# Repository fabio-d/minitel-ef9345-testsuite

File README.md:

# EF9345/TS9347 test suite

This repository contains a test suite for emulators of the
[EF9345](https://en.wikipedia.org/wiki/Thomson_EF9345) and TS9347 video chips,
such as the one included in the [MAME project](https://www.mamedev.org/).

These video chips provided the graphic capabilities of many French
[Minitels](https://en.wikipedia.org/wiki/Minitel) in the 80s and 90s.

The tests in this repository can be run both against MAME (see
[emu_mame](emu_mame) subfolder) and against real chips, through a custom USB
adapter board (see [hw_devboard](hw_devboard) subfolder).

While it is possible (and, currently, expected) that some tests may not pass on
MAME, all the tests have been verified on real chips.

## License

Same as MAME, i.e. [GNU General Public License version 2](LICENSE) or later.

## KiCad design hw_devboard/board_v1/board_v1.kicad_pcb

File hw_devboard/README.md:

# Hardware board: USB EF9345/TS9347 Video Adapter

This folder contains the schematics, firmware and host software for running the
test suite against real EF9345 and TS9347 chips using a custom board.

## Board description

The custom boards host the video chip (either EF9345P or TS9347CP/2R00), a 32
KiB RAM module for it to store the text buffers and a 74LS373N latch to
demultiplex RAM addresses. In addition, for the TS9347CP only, an LM393 and some
passives extract the video composite sync signal from the TS9347CP's analog Y
output.

The solder jumper pads (JP1 to JP9) on the back side of the board adapt some
internal connections to the connected video chip (the EF9345P and TS9347CP/2R00
are not pin compatible).

Jumpers JP11-JP14 make it possible to limit the available RAM size.

Bill of materials with links:

* U1: The video chip
  ([EF9345P](https://www.aliexpress.com/item/32905550985.html) or
  [TS9347CP/2R00](https://www.ebay.com/itm/281664411315)) and
  [its socket (40 pin variant)](https://www.aliexpress.com/item/1005006256010892.html).
* U2: [AS6C62256-55PCN](https://www.mouser.com/ProductDetail/913-AS6C62256-55PCN)
  SRAM and [its socket](https://www.mouser.com/ProductDetail/737-ICS-628-T).
* U3: [SN74LS373N](https://www.mouser.com/ProductDetail/595-SN74LS373N) and
  [its socket](https://www.mouser.com/ProductDetail/737-ICS-320-T).
* U4 (for the TS9347 only): LM393 and its socket (e.g. from
  [this kit](https://www.aliexpress.com/item/1005007032661721.html)).
* RV1 (for the TS9347 only): 200 kOhm RM065 potentiometer (e.g. from
  [this kit](https://www.aliexpress.com/item/1005006182414764.html)).
* R1 (for the TS9347 only): 220 kOhm resistor.
* R2 (for the TS9347 only): 4.7 kOhm resistor.
* C1 and C2 (for the TS9347 only): 10 uF electrolitic capacitors.
* 2.54 mm male and female pin headers (e.g. from
  [this kit](https://www.aliexpress.com/item/1005006034877497.html)).
* 3 (EF9345) or 4 (TS9347) 2.54 mm jumpers (e.g. from
  [this kit](https://www.aliexpress.com/item/4000583368141.html)).

In addition, the board itself needs to be mounted on the
[EZ-USB FX2LP development board](https://www.aliexpress.com/item/1005005100640836.html),
which provides the high-speed USB interface to both read/write the video chip's
registers and, most importantily, streaming the real-time video signal back to
the host computer at 12 MiB/s.

### EZ-USB FX2LP board pinout

| FX2 pin     | EF9345P pin | TS9347CP/2R00 pin | Description                  |
|-------------|-------------|-------------------|------------------------------|
| **Outputs:**                                                              ||||
| CTL0 (J2.16)| CLK (12)    | CLK (12)          | Video Chip Clock             |
| PA3 (J2.10) | AS (14)     | AS (14)           | Address Strobe (aka ALE)     |
| PA4 (J2.9)  | DS (15)     | DS (15)           | Data Strobe (aka ~RD)        |
| PA5 (J2.8)  | R/~W (16)   | R/~W (16)         | Read/Write (aka ~WR)         |
| PA6 (J2.7)  | ~CS (26)    | ~CS (20)          | Chip Select                  |
| **Inputs:**                                                               ||||
| PB0 (J1.15) | I (10)      | G (10)            | Video Signal Value (digital) |
| PB1 (J1.16) | R (9)       | R (9)             | Video Signal Value (digital) |
| PB2 (J1.17) | G (8)       | B (8)             | Video Signal Value (digital) |
| PB3 (J1.18) | B (7)       | not connected     | Video Signal Value (digital) |
| PB6 (J2.18) |             |                   | CTL0 loopback (for debug)    |
| PB7 (J2.17) | HVS/HS (5)  | Y (7) via LM393   | Video Signal Composite Sync  |
| **Bidirectional:**                                                        ||||
| PD0 (J2.5)  | AD0 (17)    | AD0 (17)          | Multiplexed Address/Data Bus |
| PD1 (J2.4)  | AD1 (18)    | AD1 (18)          | Multiplexed Address/Data Bus |
| PD2 (J2.3)  | AD2 (19)    | AD2 (19)          | Multiplexed Address/Data Bus |
| PD3 (J2.2)  | AD3 (21)    | AD3 (21)          | Multiplexed Address/Data Bus |
| PD4 (J2.1)  | AD4 (22)    | AD4 (22)          | Multiplexed Address/Data Bus |
| PD5 (J1.1)  | AD5 (23)    | AD5 (23)          | Multiplexed Address/Data Bus |
| PD6 (J1.2)  | AD6 (24)    | AD6 (24)          | Multiplexed Address/Data Bus |
| PD7 (J1.3)  | AD7 (25)    | AD7 (25)          | Multiplexed Address/Data Bus |

Note: When EZ-USB's J3 jumper is inserted, PA0 and PA1 control the on-board LEDs
(respectively D1 and D2). Our firmware reports what kind of chip it detected
through these LEDs: EF9345 = D1 on, TS9347 = D2 on, detection failed = both on.

### Schematic

## Customization

Before using the board, some customizations are necessary.

### Selecting the video chip

JP1 to JP9 on the back side of the board need to be bridged with solder,
depending on the type of video chip to be tested:

* each JPx must be bridged to the left (i.e. by shorting pads 1 and 2) for the
  EF9345P, like in the picture above.
* each JPx must be bridged to the right (i.e. by shorting pads 2 and 3) for the
  TS9347CP/2R00, symmetrical to the picture above.

In addition, for the TS9347CP only, the RV1 potentiometer must be adjusted so
that its middle pin gives about 0.456 V (to tell the SYNC and BLACK levels
apart, see the "REFERENCE LEVEL" table in the TS9347 datasheet).

### Selecting the video RAM size

Provided neither long codes nor custom fonts are used, the EF9345 and TS9347 can
operate with as little as just 2 KiB of video RAM.

While the AS6C62256-55PCN RAM IC contains 32 KiB of RAM, it is possible to mask
some of its address lines through jumpers JP11-JP14 to make it appear smaller.
The following configurations are possible:

<table>
  <tr>
    <td align="center"><br />2 K</td>
    <td align="center"><br />4 K</td>
    <td align="center"><br />8 K</td>
    <td align="center"><br />16 K</td>
    <td align="center"><br />32 K</td>
  </tr>
</table>

Note 1: JP14 is ignored and can be left unpopulated in the case of the EF9345
chip, as EF9345 only supports up to 16 KiB.

Note 2: current and future tests will assume that all the jumpers are connected
to the right (i.e. maximum possible RAM size).

### Getting 5 V power from the EZ-USB FX2LP development board

All the chips on our board (including, notably, the video chip) need to be
powered at 5 V. The USB power supply provided from the host would be suitable
(the USB bus provides power at exactly 5 V) but, unfortunately, no pin of the
EZ-USB FX2LP development board exposes the USB's 5 V line.

Therefore, in order to connect USB's 5 V to our board, we need to apply a small
mod to the EZ-USB FX2LP board by soldering and connecting a wire as shown in the
following images:

Note: by soldering the wire in the way shown above, the power switch on the
front of the EZ-USB FX2LP board will be in control of our derived 5 V rail too.

### Supporting software

Prerequisites:

```shell
$ git submodule init && git submodule update  # to checkout firmware/fx2lib
$ sudo apt install build-essential cycfx2prog libusb-1.0-0-dev qt6-base-dev sdcc
```

Firmware for the FX2LP chip is provided in the `firmware` subdirectory and it
can be compiled and then loaded over USB into the board with:

```shell
$ cd hw_devboard/firmware
$ make
$ sudo cycfx2prog prg:build/firmware.ihx run
```

The above `cycfx2prog` command will load the firmware into the FX2LP's RAM and
execute it from there. It will not persist after power cycling.

The `host_connector_gui` program can then be started on the host:

```shell
$ cd hw_devboard/host_connector_gui
$ qmake6
$ make
$ sudo ./host_connector_gui
```

## Running the tests

After loading the firmware and opening the `host_connector_gui` program, select
*Device* &rarr; *Connect...* to locate the USB board, then *Device* &rarr;
*Enable TCP Server...* and confirm the default listen address `127.0.0.1:1234`.

Finally, run a test (e.g. `test_resolutions.py`) with:

```shell
$ cd ../tests
$ python3 test_resolutions.py --video-chip 127.0.0.1:1234
```

## Gallery

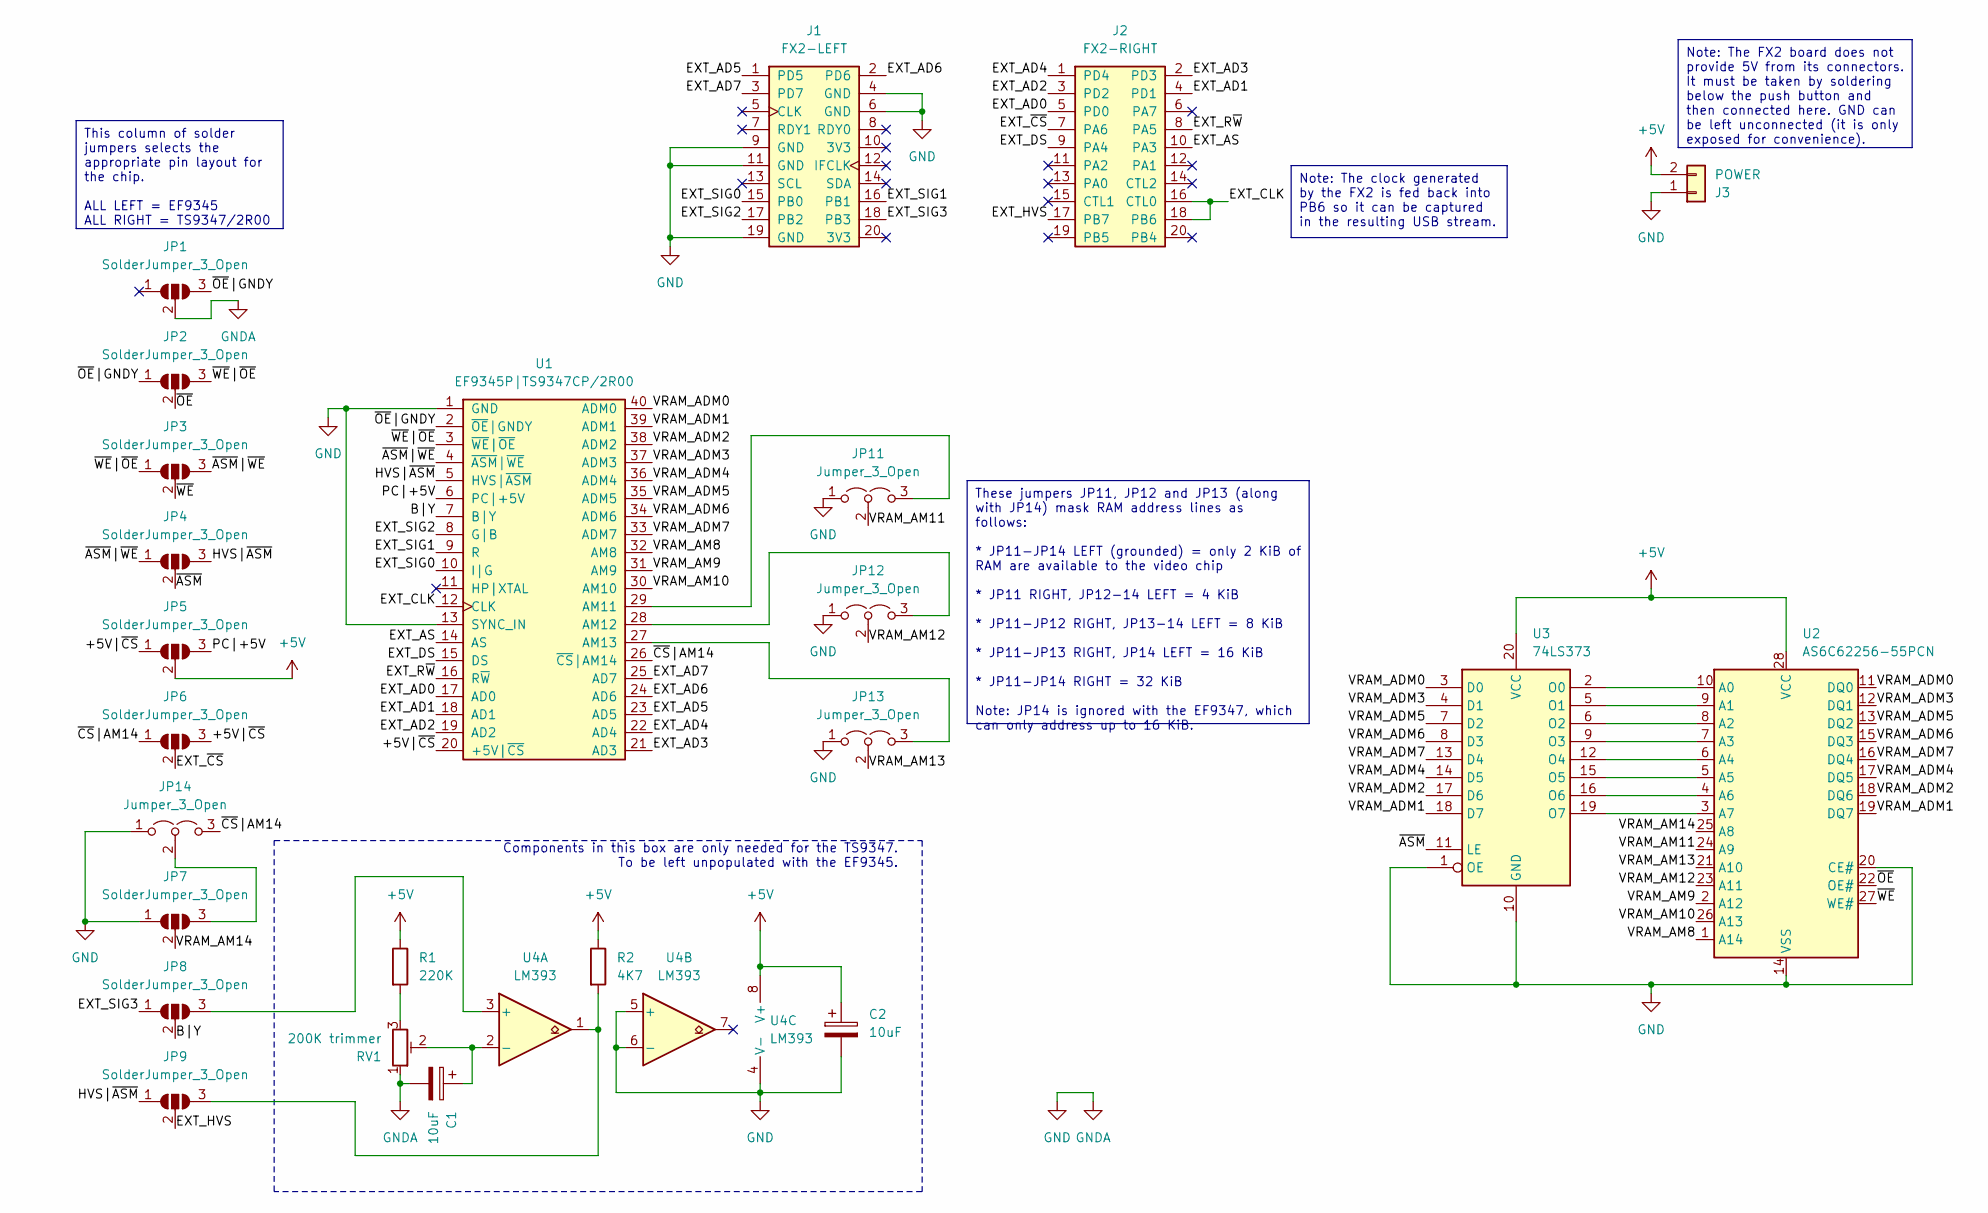
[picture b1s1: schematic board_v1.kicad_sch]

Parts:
C1, C2: 10uF; CP_Radial_D5.0mm_P2.50mm
J1: FX2-LEFT; PinHeader_2x10_P2.54mm_Vertical
J2: FX2-RIGHT; PinHeader_2x10_P2.54mm_Vertical
J3: POWER; PinHeader_1x02_P2.54mm_Vertical
JP1, JP2, JP3, JP4, JP5, JP6, JP7, JP8, JP9: SolderJumper_3_Open; SelectorJumper
JP11, JP12, JP13, JP14: Jumper_3_Open; PinHeader_1x03_P2.54mm_Vertical
R1: 220K; R_Axial_DIN0309_L9.0mm_D3.2mm_P12.70mm_Horizontal
R2: 4K7; R_Axial_DIN0309_L9.0mm_D3.2mm_P12.70mm_Horizontal
RV1: 200K trimmer; Potentiometer_Runtron_RM-065_Vertical
U1: EF9345P|TS9347CP/2R00; DIP-40_W15.24mm_Socket
U2: AS6C62256-55PCN; DIP-28_W15.24mm
U3: 74LS373; DIP-20_W7.62mm_Socket
U4: LM393; DIP-8_W7.62mm_Socket

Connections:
+5V: C2.1, J3.2, JP5.2 (C), R1.1, R2.1, U2.28 (VCC), U3.20 (VCC), U4.8 (V+)
/+5V|~CS: JP5.1 (A), JP6.3 (B), U1.20 (+5V|~CS)
/B|Y: JP8.2 (C), U1.7 (B|Y)
/EXT_AD0: J2.5 (PD0), U1.17 (AD0)
/EXT_AD1: J2.4 (PD1), U1.18 (AD1)
/EXT_AD2: J2.3 (PD2), U1.19 (AD2)
/EXT_AD3: J2.2 (PD3), U1.21 (AD3)
/EXT_AD4: J2.1 (PD4), U1.22 (AD4)
/EXT_AD5: J1.1 (PD5), U1.23 (AD5)
/EXT_AD6: J1.2 (PD6), U1.24 (AD6)
/EXT_AD7: J1.3 (PD7), U1.25 (AD7)
/EXT_AS: J2.10 (PA3), U1.14 (AS)
/EXT_CLK: J2.16 (CTL0), J2.18 (PB6), U1.12 (CLK)
/EXT_DS: J2.9 (PA4), U1.15 (DS)
/EXT_HVS: J2.17 (PB7), JP9.2 (C)
/EXT_R~W: J2.8 (PA5), U1.16 (R~W)
/EXT_SIG0: J1.15 (PB0), U1.10 (I|G)
/EXT_SIG1: J1.16 (PB1), U1.9 (R)
/EXT_SIG2: J1.17 (PB2), U1.8 (G|B)
/EXT_SIG3: J1.18 (PB3), JP8.1 (A)
/EXT_~CS: J2.7 (PA6), JP6.2 (C)
/HVS|~ASM: JP4.3 (B), JP9.1 (A), U1.5 (HVS|~ASM)
/PC|+5V: JP5.3 (B), U1.6 (PC|+5V)
/VRAM_ADM0: U1.40 (ADM0), U2.11 (DQ0), U3.3 (D0)
/VRAM_ADM1: U1.39 (ADM1), U2.19 (DQ7), U3.18 (D7)
/VRAM_ADM2: U1.38 (ADM2), U2.18 (DQ6), U3.17 (D6)
/VRAM_ADM3: U1.37 (ADM3), U2.12 (DQ1), U3.4 (D1)
/VRAM_ADM4: U1.36 (ADM4), U2.17 (DQ5), U3.14 (D5)
/VRAM_ADM5: U1.35 (ADM5), U2.13 (DQ2), U3.7 (D2)
/VRAM_ADM6: U1.34 (ADM6), U2.15 (DQ3), U3.8 (D3)
/VRAM_ADM7: U1.33 (ADM7), U2.16 (DQ4), U3.13 (D4)
/VRAM_AM8: U1.32 (AM8), U2.1 (A14)
/VRAM_AM9: U1.31 (AM9), U2.2 (A12)
/VRAM_AM10: U1.30 (AM10), U2.26 (A13)
/VRAM_AM11: JP11.2 (C), U2.24 (A9)
/VRAM_AM12: JP12.2 (C), U2.23 (A11)
/VRAM_AM13: JP13.2 (C), U2.21 (A10)
/VRAM_AM14: JP7.2 (C), U2.25 (A8)
/~ASM: JP4.2 (C), U3.11 (LE)
/~ASM|~WE: JP3.3 (B), JP4.1 (A), U1.4 (~ASM|~WE)
/~CS|AM14: JP6.1 (A), JP14.3 (B), U1.26 (~CS|AM14)
/~OE: JP2.2 (C), U2.22 (OE#)
/~OE|GNDY: JP1.3 (B), JP2.1 (A), U1.2 (~OE|GNDY)
/~WE: JP3.2 (C), U2.27 (WE#)
/~WE|~OE: JP2.3 (B), JP3.1 (A), U1.3 (~WE|~OE)
GND: C1.2, C2.2, J1.4 (GND), J1.6 (GND), J1.9 (GND), J1.11 (GND), J1.19 (GND), J3.1, JP1.2 (C), JP7.1 (A), JP11.1 (A), JP12.1 (A), JP13.1 (A), JP14.1 (A), RV1.1, U1.1 (GND), U1.13 (SYNC_IN), U2.14 (VSS), U2.20 (CE#), U3.1 (OE), U3.10 (GND), U4.4 (V-), U4.5 (+), U4.6 (-)
unnamed: JP8.3 (B), U4.3 (+)
unnamed: JP9.3 (B), R2.2, U4.1
unnamed: JP11.3 (B), U1.29 (AM11)
unnamed: JP12.3 (B), U1.28 (AM12)
unnamed: JP13.3 (B), U1.27 (AM13)
unnamed: JP7.3 (B), JP14.2 (C)
unnamed: R1.2, RV1.3
unnamed: U2.10 (A0), U3.2 (O0)
unnamed: U2.9 (A1), U3.5 (O1)
unnamed: U2.8 (A2), U3.6 (O2)
unnamed: U2.7 (A3), U3.9 (O3)
unnamed: U2.6 (A4), U3.12 (O4)
unnamed: U2.5 (A5), U3.15 (O5)
unnamed: U2.4 (A6), U3.16 (O6)
unnamed: U2.3 (A7), U3.19 (O7)
unnamed: C1.1, RV1.2, U4.2 (-)

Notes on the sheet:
Note: The clock generated by the FX2 is fed back into PB6 so it can be captured in the resulting USB stream.
These jumpers JP11, JP12 and JP13 (along with JP14) mask RAM address lines as follows: * JP11-JP14 LEFT (grounded) = only 2 KiB of RAM are available to the video chip * JP11 RIGHT, JP12-14 LEFT = 4 KiB * JP11-JP12 RIGHT, JP13-14 LEFT = 8 KiB * JP11-JP13 RIGHT, JP14 LEFT = 16 KiB * JP11-JP14 RIGHT =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
Note: The FX2 board does not provide 5V from its connectors. It must be taken by soldering below the push button and then connected here. GND can be left unconnected (it is only exposed for convenience).
This column of solder jumpers selects the appropriate pin layout for the chip. ALL LEFT = EF9345 ALL RIGHT = TS9347/2R00
Components in this box are only needed for the TS9347. To be left unpopulated with the EF9345.

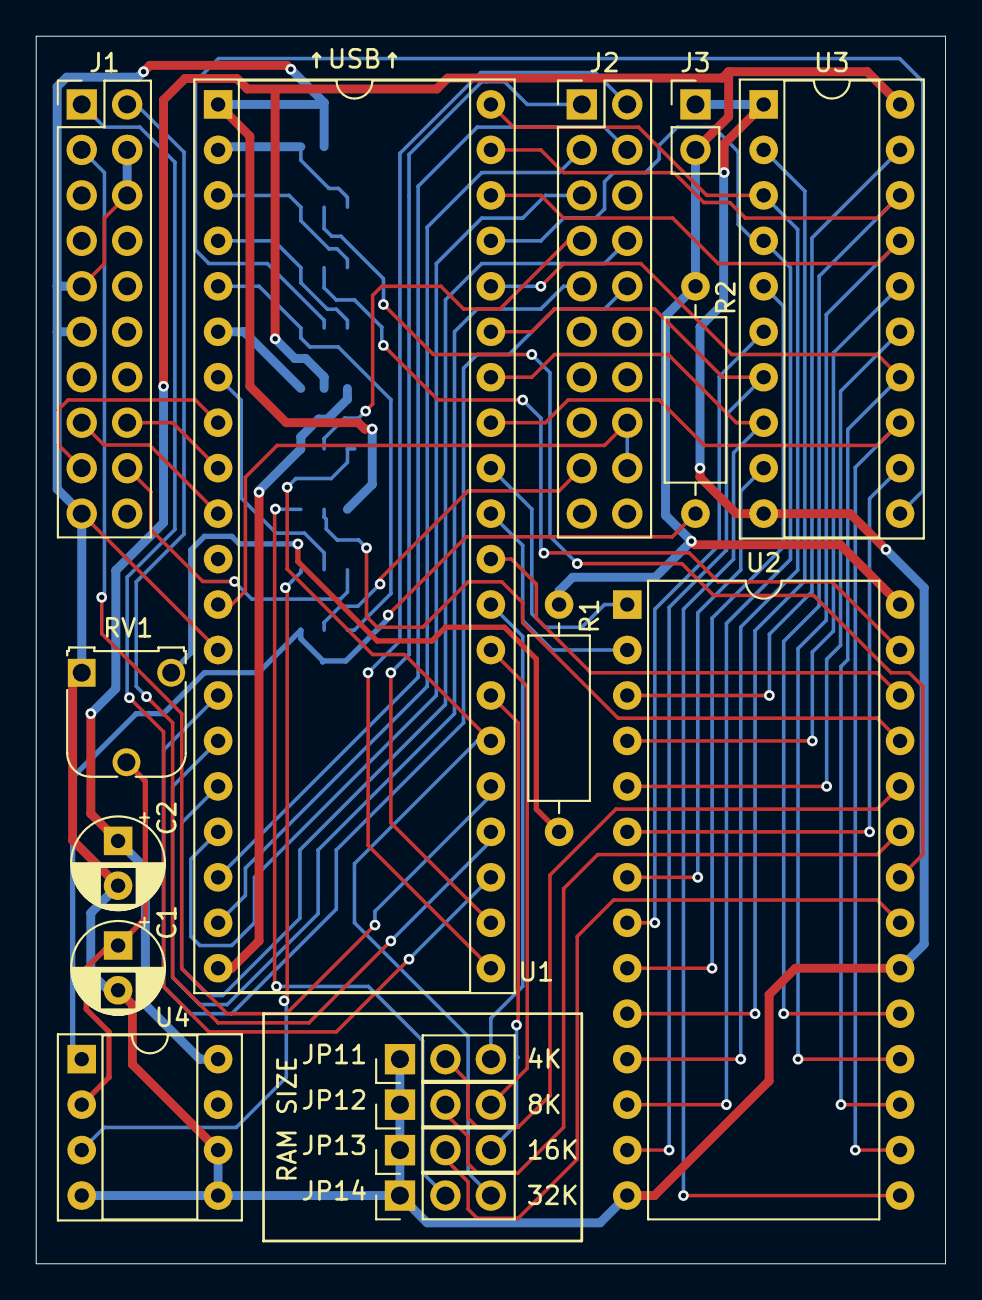
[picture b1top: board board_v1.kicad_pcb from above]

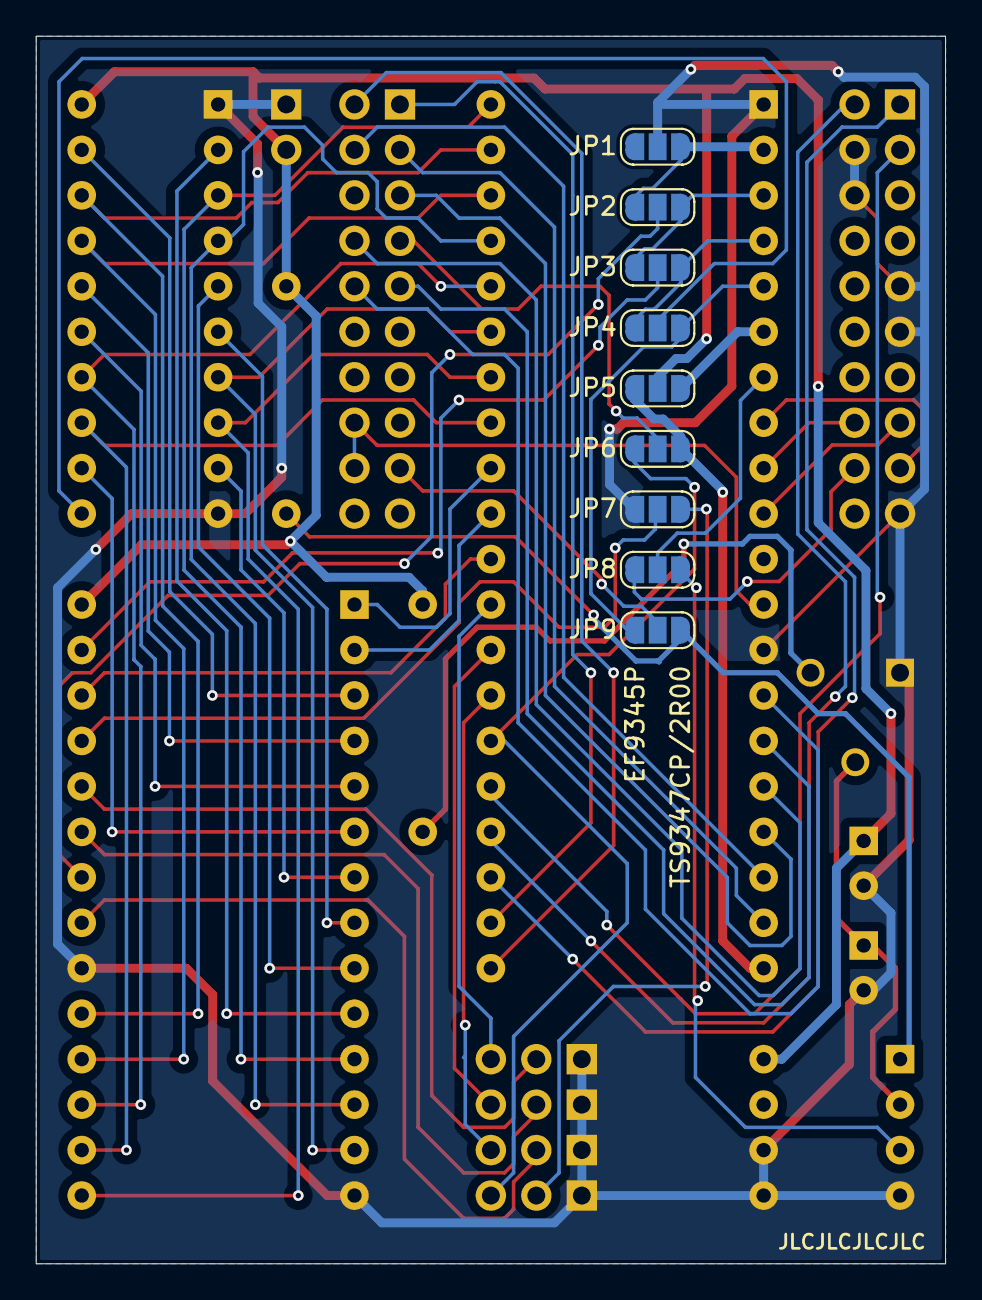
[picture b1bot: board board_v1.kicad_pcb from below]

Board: 2 copper layers, 50.8 x 68.6 mm, 25 parts (9 on the bottom side), 62 nets.

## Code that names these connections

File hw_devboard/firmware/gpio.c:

#include "gpio.h"

#include <delay.h>
#include <fx2regs.h>

#define LED_D1 PA0        // On-board LED (0=on, 1=off)
#define LED_D2 PA1        // On-board LED (0=on, 1=off)
#define BUS_ALE PA3       // To AS of video chip
#define BUS_nRD PA4       // To DS of video chip
#define BUS_nWR PA5       // To R/nW of video chip
#define BUS_nCS PA6       // To nCS of video chip
#define BUS_ADDR_DATA IOD // To ADM pins of video chip

#define BUS_DRIVE(value)                                                       \
  do {                                                                         \
    BUS_ADDR_DATA = value;                                                     \
    OED = 0xff;                                                                \
  } while (false)

#define BUS_HIGH_Z()                                                           \
  do {                                                                         \
    OED = 0x00;                                                                \
  } while (false)

void gpio_setup(void) {
  // Set initial output values.
  BUS_ALE = 0;
  BUS_nRD = 1;
  BUS_nWR = 1;
  BUS_nCS = 1;

  // Set initial pin directions.
  OEA = 0b01111011;
  OED = 0x00;
}

void set_led1(bool on) {
  LED_D1 = !on;
}

void set_led2(bool on) {
  LED_D2 = !on;
}

uint8_t bus_read(uint8_t address) {
  BUS_ALE = 1;
  BUS_DRIVE(address);
  BUS_nCS = 0;
  SYNCDELAY2;
  BUS_ALE = 0;
  SYNCDELAY2;
  BUS_HIGH_Z();
  BUS_nCS = 1;
  SYNCDELAY2;
  BUS_nRD = 0;
  SYNCDELAY2;
  uint8_t result = BUS_ADDR_DATA;
  BUS_nRD = 1;
  SYNCDELAY2;
  return result;
}

void bus_write(uint8_t address, uint8_t data) {
  BUS_ALE = 1;
  BUS_DRIVE(address);
  BUS_nCS = 0;
  SYNCDELAY2;
  BUS_ALE = 0;
  SYNCDELAY2;
  BUS_nCS = 1;
  SYNCDELAY2;
  BUS_nWR = 0;
  BUS_DRIVE(data);
  SYNCDELAY2;
  BUS_nWR = 1;
  SYNCDELAY2;
  BUS_HIGH_Z();
}

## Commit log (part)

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2025-03-09 Apply formatting rules
2025-03-09 Add KiCad project for hardware board
2025-03-09 Test output resolution and RGB color channels
2025-03-09 Expose the registers and video output of MAME's emulated TS9347 over TCP
2025-03-09 Make the SVG schematic readable with dark themes too
    Set the background color to white (instead of transparent)
2025-03-16 Add host program to control the hardware board
2025-03-16 Test resolutions that are only possible with the EF9345
2025-03-16 Format C++ files too
2025-03-16 Format C header files too
2025-03-16 Add firmware for the hardware board
2025-03-16 More detailed readme for hardware board
2025-03-16 Test rendering of all possible characters
2025-03-23 Improve color test by testing the attributes too
2025-03-23 Add more font tests
2025-03-23 Add support for parametric tests
2025-03-23 Fill missing value in hardware board's README
2025-03-23 Set TCP_NODELAY on the VideoChip socket
    This makes command round trips considerably faster.
2025-03-23 Optionally filter tests from the command line
2025-03-23 Store screenshots with flashing parts as APNG files
    This commit also changes slightly the way we compare
    screenshots against their template.
2025-04-06 Do not scale the image in the host controller window by default
    To avoid aliasing in the default configuration.
2025-04-06 Add script to unpack and repack animated PNGs
2025-04-06 Validate "insert" channel too
2025-04-20 Test cursor rendering in 40 column mode
2025-04-20 Make test_40columns_attributes parametric
2025-04-20 Cleanup unused imports
2025-04-20 Interpret filters as wildcard patterns
2025-04-20 Stop executing tests if CTRL-C is pressed
2025-04-26 Test underline cursor on non-alphanumeric characters
2025-04-26 Test cursor rendering in 80 column mode
2025-04-26 Test color attributes in 80 column mode
2025-04-26 Adjust crop box for 80 columns mode of TS9347
    The bulk area seems to start and end one pixel earlier than the EF9345
2025-04-27 Test busy bit in status register
2025-04-27 Test rendering of size attributes
2025-04-27 Adjust crop box for 80 columns mode in MAME
2025-04-27 Add flag to optionally show MAME's window instead of hiding it
2025-04-27 Test cursor rendering in conjunction with size attributes
2025-08-18 Fix typo in comment
2025-08-18 Fix missing wait in test_80columns_attributes
2025-08-18 Start counting time only after waiting in test_not_busy
2025-08-23 Test rendering of double-sized characters with differing values
2025-08-23 Test address transcoding
2025-08-23 Test clear page commands
2025-08-23 Validate the effect of double-size attributes in the service row
2025-08-23 Add missing waits in test_size
2025-09-06 Remove KiCad file containing local data (.kicad_prl)
2025-10-26 Test double-height attribute crossing different areas of the screen
2025-10-26 Test rendering when bulk areas and service row are toggled
2025-12-14 Fix typing annotation
2025-12-14 Test memory read/write commands
    Thanks to:
    - IapetusRetroStuff for analyzing the Y incrementation.
    - EcrouVis for suggesting a way to test undocumented commands.
2025-12-14 Test isolated character with double-width attribute
